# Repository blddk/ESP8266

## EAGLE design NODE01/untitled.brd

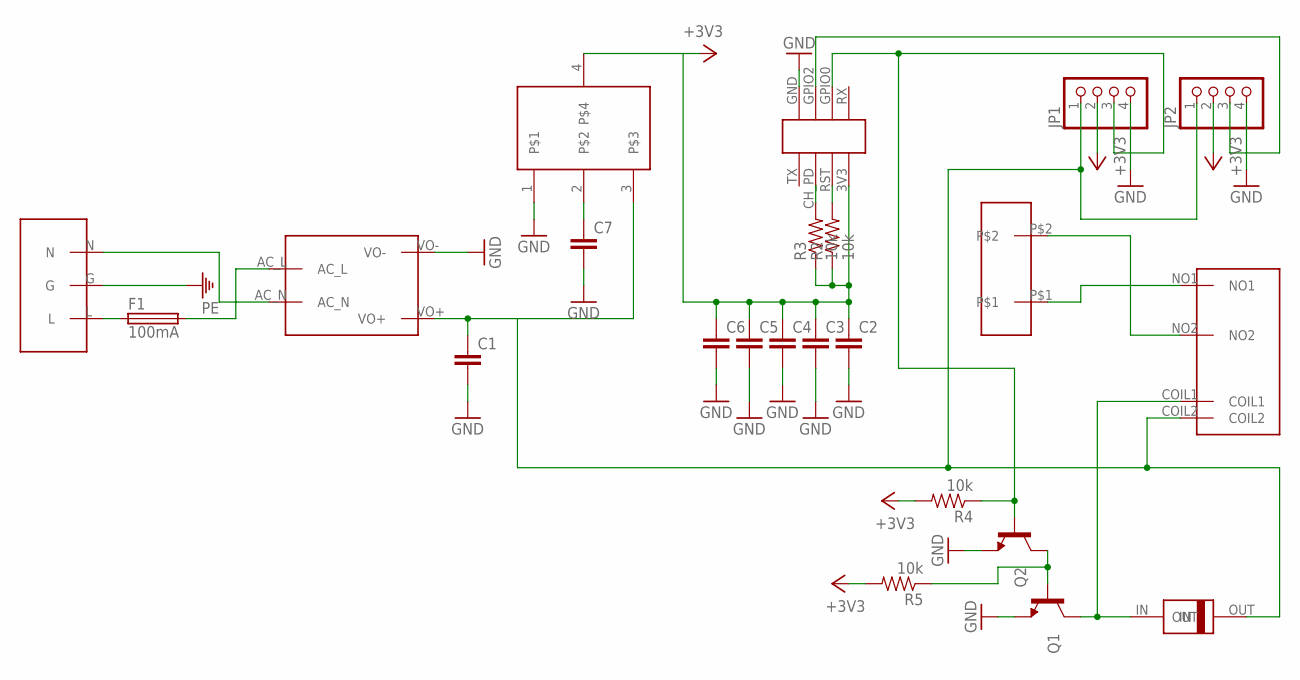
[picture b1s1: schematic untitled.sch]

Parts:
C1, C2, C3, C4, C5, C6, C7: CAP0805; 0805
DIODE1: DIODE_1N4148WQ-7-F
F1: 100mA; SH22,5A
JP1, JP2: PINHD-1X4; 1X04
Q1, Q2: TRANSISTOR_NPNSOT23; SOT23
R2, R3, R4, R5: 10k; 0603-RES
U$1: MAINS_CONVERTERS; HLK-PM01
U$2: SCREWTERMINALS_5MM; 3PIN_LNG
U$4: VREG; SOT223
U$5: SCREWTERMINALS_5MM_2; TERMINAL_2X
U$6: OMRON_G6M-1A
U$7: ESP8266-01

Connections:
+3V3: C2.1, C3.1, C4.1, C5.1, C6.1, JP1.2, JP2.2, R2.1, R3.1, R4.2, R5.2, U$4.4, U$7.3V3
GND: C1.2, C2.2, C3.2, C4.2, C5.2, C6.2, C7.2, JP1.4, JP2.4, Q1.2 (E), Q2.2 (E), U$1.VO-, U$4.1, U$7.GND
unnamed: F1.2, U$1.AC_L
unnamed: U$1.AC_N, U$2.N
unnamed: F1.1, U$2.L
unnamed: C1.1, DIODE1.OUT, JP1.1, JP2.1, U$1.VO+, U$4.3, U$6.COIL2
unnamed: Q1.1 (B), Q2.3 (C), R5.1
unnamed: U$5.P$2, U$6.NO2
unnamed: U$5.P$1, U$6.NO1
unnamed: DIODE1.IN, Q1.3 (C), U$6.COIL1
unnamed: JP2.3, U$7.GPIO2
unnamed: R2.2, U$7.RST
unnamed: C7.1, U$4.2
unnamed: JP1.3, Q2.1 (B), R4.1, U$7.GPIO0
unnamed: R3.2, U$7.CH_PD
PE: U$2.G

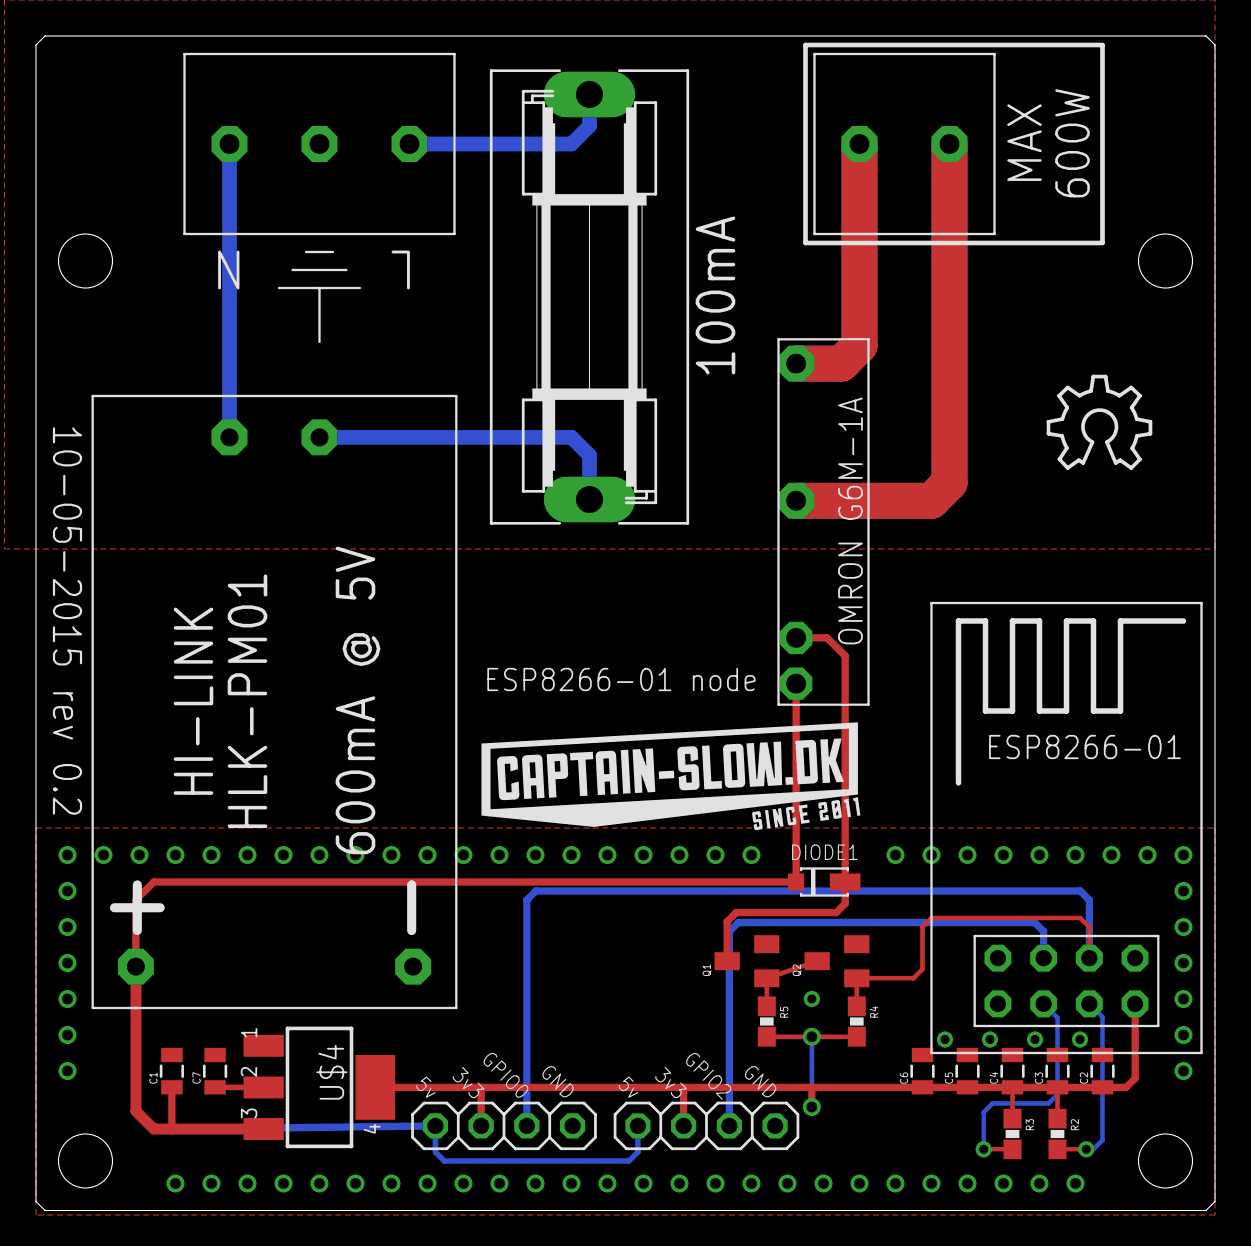
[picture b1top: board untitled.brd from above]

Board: 2 copper layers, 65.5 x 65.2 mm, 25 parts (0 on the bottom side), 15 nets.

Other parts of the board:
U$3: OSHW_8X200_NOTEXT
U$8: CAPTAIN_SLOW_SMALL

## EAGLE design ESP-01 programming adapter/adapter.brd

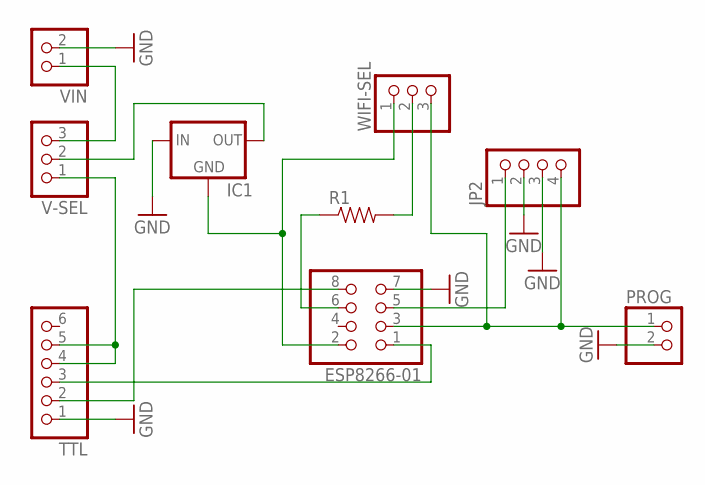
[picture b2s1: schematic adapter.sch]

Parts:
ESP8266-01: PINHD-2X4; 2X04
IC1: V_REG_78XXSIDE; 78XXL
JP2: PINHD-1X4; 1X04
PROG: PINHD-1X2; 1X02
R1: RESISTORAXIAL-0.3; AXIAL-0.3
TTL: PINHD-1X6; 1X06
V-SEL: PINHD-1X3; 1X03
VIN: PINHD-1X2; 1X02
WIFI-SEL: PINHD-1X3; 1X03

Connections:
GND: ESP8266-01.7, IC1.IN, JP2.2, JP2.3, PROG.2, TTL.1, VIN.2
unnamed: ESP8266-01.2, IC1.GND, WIFI-SEL.1
unnamed: ESP8266-01.8, TTL.2
unnamed: ESP8266-01.1, TTL.3
unnamed: TTL.4, TTL.5, V-SEL.1
unnamed: ESP8266-01.3, JP2.4, PROG.1, WIFI-SEL.3
unnamed: V-SEL.3, VIN.1
unnamed: ESP8266-01.6, R1.P$1 (1)
unnamed: ESP8266-01.5, JP2.1
unnamed: R1.P$2 (2), WIFI-SEL.2
unnamed: IC1.OUT, V-SEL.2

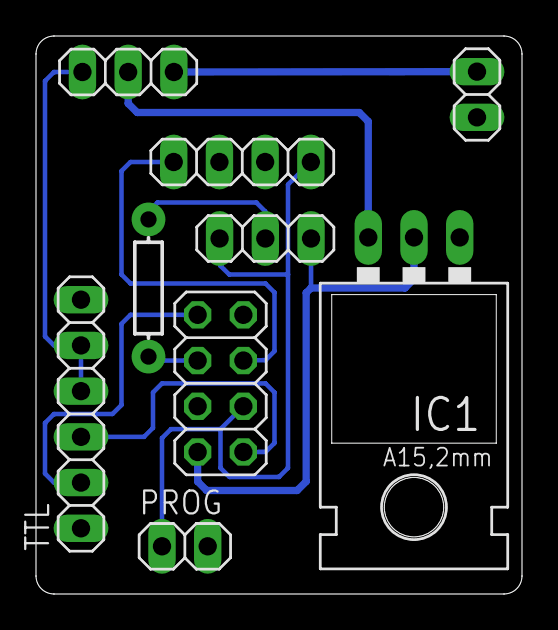
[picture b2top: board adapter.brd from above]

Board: 2 copper layers, 27.0 x 31.0 mm, 9 parts (0 on the bottom side), 11 nets.

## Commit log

2015-04-03 :boom::camel: Added .gitattributes & .gitignore files
2015-04-03 CH_PD
    Added resistor and jumper to the CH_PD pin, allowing for either
    connecting it to VCC for constant on, or to connect it to GPIO00 for
    controlling it by code.
2015-04-03 Voltage regulator pin out
    Changed pin out on the voltage regulator to fit TI LM1117 TO-220 package
    http://www.ti.com/lit/ds/symlink/lm1117-n.pdf
2015-04-04 CH_PD
    Pin connected to GPIO00 instead of 02, so GPIO02 is free to do external
    triggers.
2015-04-05 Slim
    Added version with very thin traces for easier milling
2015-04-05 oops
    Missed one trace
2015-09-27 Create Node 01
2015-09-27 Initial upload

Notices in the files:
parts and their libraries:
SparkFun-PowerIC: Licensing: CC v3.0 Share-Alike You are welcome to use this library for commercial purposes.
